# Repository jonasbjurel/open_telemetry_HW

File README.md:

# open_telemetry_HW

**Licenses:**

The official OpenFly Telemetry project(s) are all open source. The licensing may vary from GPL 2, GPL 3, Apache, or Creative Commons. As with many other hardware projects – OpenFly Telemetry comes with the Creative Commons - CC BY 2.0 license.

**Disclaimers:**

The use of any HW, SW or instructions from the OpenFly Telemetry open source project, or any references to other art - is at your own risk. No warranties, or legal obligations shall be assumed from the creators – in any way. Flying model planes, drones or other remotely controlled vehicles always impose danger to the surroundings – make all necessary precautions to make sure that no one is in danger even in case the control of your model is lost for whatever reason.

# Latest news
OFT001v1P1A* with sample BIST SW have declared it's first release candidate February 04 - 2020. First prototype full release is expected during February 2020. See the Wiki for mor information: https://github.com/jonasbjurel/open_telemetry_HW/wiki

# WIKI
 https://github.com/jonasbjurel/open_telemetry_HW/wiki

# OpenFly Telemetry overview
OpenFly Telemetry is an open source project aiming to provide telemetry and navigation capabilities for model airplanes and drones through open source hardware and software. It uses various on-board sensor capabilities such as GPS, Accelerometers, Gyroscopes, Magnetometers, Pitot tubes, temperature sensors, battery voltage and current sensors, RPM sensors, etc. to provide the operator or algorithms with data for manual or automated corrective actions. The algorithms are some time autonomous and resides in the model, are sometimes on ground with the receiver or nearby connected devices or are sometimes even in distant clouds.
The OFT modules can also be placed in the module bay of the transmitter to enrich the transmitter awareness, e.g. Position, direction and additional communication capabilities such as Bluetooth and WIFI conectivity.

**Figure 1:** OpenFly Telemetry basic idea

# OpenFly Telemetry (OFT) system description
OFT has two basic components: the Ada fruit ESP32 Huzzah feather processor board and the OFT system board. The ESP32 processor board obviously holds the software and algorithms for telemetry and navigation. The system board interfaces with the radio receiver and its telemetry and servo busses. The system is modular, and you can compose your choice of capabilities by stacking various OFT sensor boards on top of each other.

**Figure 2:** OpenFly Telemetry system view

OFT is based out of the Ada fruit ESP32 Huzzah feather processor board. This board hosts an ESP32 processor with two 32-bit general processor cores, 2 float processors and one ultra-low-power co-processor from Espressif (https://www.espressif.com/). Furthermore, the ESP32 board provides wireless connectivity through Bluetooth and WIFI as well as ensuring continuous power supply through an optional 2S designated LIPO, which could temporarily feed the servos and the receiver- should the main supply drain.
The ESP32 mother board connects to several telemetry acquisition boards in mother-daughter board/shield configurations.

**Figure 3:** Ada fruit ESP32 Huzzah feather board

For the on-board use cases (as opposed to the TX bay use case), the bottom most shield in the stack holds the OFT System board. The system board has an FPGA that connects to the radio receiver through the S.PORT for telemetry data, and the SBUS for servo output. The FPGA will allow the ESP32 processor to mix in servo corrections from the processor, transmitting upstream telemetry data, as well as receiving upstream telemetry and servo information from the transmitter. 
The system board interconnects with the radio control receiver through its S.PORT and SBUS.

**Figure 4:** Frsky XR4 2.4 GHz MIMO CDMA receiver with S.PORT- (telemetry) and SBUS (Servos) connections

# OpenFly Telemetry resources
## OpenFly Telemetry repositories
[OpenFly Telemetry main applications repository](https://github.com/jonasbjurel/open_telemetry)
This repository provides the application software repository for the OpenFly Telemetry project.

[OpenFly Telemetry hardware repository](https://github.com/jonasbjurel/open_telemetry_HW)
The repository for this project - providing HW blue-prints and designs for OpenFly Telemetry.

##  OpenFly Telemetry Dependencies
[ESP32 Arduino](https://github.com/espressif/arduino-esp32)
The Arduino port of Espressif ESP32.

[ESP32 FreeRTOS port documentation](https://docs.espressif.com/projects/esp-idf/en/latest/api-reference/system/freertos.html) FreeRTOS APIs and methods available for ESP32

[High availability- and embedded system FreeRTOS  shim layer](https://github.com/jonasbjurel/coreNoStopRTOS)
System initialization, process monitoring, memory management, system bus arbitration, inter process communication, and much more..

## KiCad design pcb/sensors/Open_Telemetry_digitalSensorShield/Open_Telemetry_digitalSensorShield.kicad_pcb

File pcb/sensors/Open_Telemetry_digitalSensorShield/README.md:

# OFT001v1 Inertial navigation board 
The OFT001v1 Inertial navigation board captures navigational data, such as GPS positioning, 3D acceleration data, 3D Gyroscopic data, 3D Magnetic data, Barometric pressure, Temperature and Humidity. Those data are provided to the ESP32 processor card (and any other shield cards) through I2C and RS232. The data will be filtered, processed and transferred by the ESP32 card and the OFT System card FPGA. It is still to be seen if we can/will implement a high-performance Inertial navigation fuse fixed point Kalman filter in the FPGA, or if it is better done in SW?

**Figure 5:** OFT001v1 Inertial navigation card overview

The OFT001v1 card has an L80-M39 GPS with a built-in patch antenna, and an optional connector for an external 50 Ohm active antenna; an MP-9250 3D axis for each of: Accelerometer, Gyroscope and Magnetometer; and a BMP280 Barometric pressure- humidity- and temperature sensor. Note that the axise's for the acelerometers and Gyrometers differs from those of the manetometers (x swaped with y, and neative Z), clearly marked on the board. The communication with these sensors have been segmented so that the MPU runs on its own high speed I2C channel, allowing fast updates, Kalman filtering-, integration- and Quaternion calculation cycles by the CPU (and possibly later offloaded by the OFT System card FPGA); the BMP280 is less latency critical, and shares an I2C channel with potentially other devices in the stack; while the GPS communication happens over an RS232 serial channel using extensions of the NMEA protocol.

There is one green LED indicator for GPS lock, one orange LED indictor for External GPS antenna use, and an RGB LED for generic system status indication driven from the ESP32 CPU board. There are also two push buttons: one which is connected to the overall system reset, and another multi-purpose push button intended for system calibration activities.

It is important that OFT001v1 sits on the top of the mother-daughter board stack (unless an external GPS antenna is used) in order to achieve a good GPS signal.
Cupper layers have been kept out from ESP32 Bluetooth and WIFI PCB antennas to not deteriorate the signal strength from those.

**Figure 6:** OFT001v1

?
## OFT001v1 shield pin-out

| OFT001 12 pin header (J2) | ESP32 HUZZAH 12 pin header (JP3) | ESP32 silicon | Comments               |
|---------------------------|----------------------------------|---------------|------------------------|
| 1 - N/C                   | VBAT                             | -             | N/C                    |
| 2 - N/C                   | EN                               | -             | N/C                    |
| 3 - N/C                   | VBUS                             | -             | N/C                    |
| 4  RED LED               | IO13_A12                         | 13 - IO13/A2_6| Red system status led  |
| 5  BLUE LED              | IO12_A11                         | 14  IO12/A2_5| Blue system status led |
| 6  GREEN LED             | IO27_A10                         | 12  IO27/A2_7| Green system status led|
| 7 - N/C                   | IO33_A9                          | 9 - IO33/A1_5 | N/C                    |
| 8 - N/C                   | IO15_A8                          | 23  IO15/A2_3| N/C                    |
| 9 - N/C                   | IO32_A7                          | 8  IO32/A1_4 | N/C                    |
| 10 - N/C                  | IO14_A6                          | 13  IO14/A2_6| N/C                    |
| 11 - I2C_0_SCL_3V         | SCL                              | 36  IO22     | Common non-critical I2C|
| 12 - I2C_0_SDA_3V         | SDA                              | 37  IO23     | Common non-critical I2C|

**Table 1:** J2 shield pin connector

| OFT001 16 pin header (J3) | ESP32 HUZZAH 16 pin header (JP1) | ESP32 silicon |Comments                   |
|---------------------------|----------------------------------|---------------|---------------------------|
| 1  INT_0                 | IO21                             | 33 - IO21     | Interrupt from MPU9250    |
| 2 - I2C_1_SDA_3V          | IO17                             | 28 - IO17     | Critical MPU I2C          |
| 3 - I2C_1_SCL_3V          | IO16                             | 27 - IO16     | Critical MPU I2C          |
| 4 - N/C                   | MISO                             | 31 - IO19     | N/C                       |
| 5 - N/C                   | MOSI                             | 30 - IO18     | N/C                       |
| 6 - N/C                   | SCK                              | 29 - IO5      | N/C                       |
| 7 - CALIB                 | A5_IO4                           | 26 - IO4/A2_2 | System calibration button |
| 8 - UART_1_CLIENT_RXD     | A4_IO36                          | 4 - IO36/A1_0 | L8-M39 GPS UART (NMEA)    |
| 9 - UART_1_CLIENT_TXD     | A3_I39                           | 5  IO39/A1_3 | L8-M39 GPS UART (NMEA)    |
| 10  N/C                  | A2_I34                           | 6  I34/A1_6  | N/C                       |
| 11  N/C                  | A1_DAC1                          | 10  IO25/DAC1/A2_8| N/C                  |
| 12  N/C                  | A0_DAC2                          | 11  IO26/DAC2/A2_9| N/C                  |
| 13 - GND                  | GND                              | -	       | GND from ESP32 motherboard|
| 14  N/C                  | N/C                              | -             | N/C                       |
| 15 - +3.3V (VDD)          | +3.3V                            | -             | 3.3V max 120 mA from ESP32 motherboard (rated for max ???)|
| 16 - RESET                | RESET                            | 3 - EN        | 2-Way reset               |

**Table 2:** J3 shield pin connector

| OFT001 Ext GPS Ant. (J1) | Comments                                                              |
|--------------------------|-----------------------------------------------------------------------|
| 1  AGND                 | External active GPS antenna ground                                    |
| 2  EXTANT               | External active GPS antenna signal with VDD DC applied for power feed |

**Table 3:** J1 External PS Antenna

## OFT001v1 addressing

| I2CBus | Addr	           | Function | Comments |
|--------|-----------------|----------|----------|
| 0	 | 0x77(0x761) (1) | BME280   | -        |
| 1      | 0x68(0x692) (2) | MPU9250  | -        |

1)	Alternative address if NULL resistor R4 is mounted (not default)
2)	Alternative address if NULL resistor R7 is mounted (not default)

**Table 4:** OFT001v1 I2C addressing

## OFT001 v1 operating specifications
### Operational conditions:

| Parameter          | Nom    | Max     | Min      |
|--------------------|--------|---------|----------|
| Voltage            | 3.3 V  | 3.6 V   | 3.0 V    |
| Current            | 30 mA  | 120 mA  | -        |
| Power dissipation  | 100 mW | 400 mW  | -        |
| Ambient temp       | -      | 85 degC | -40 degC |

**Table 5:** OFT001v1 Operational conditions

### GPS antenna operational conditions:
The built in GPS patch antenna provides the following characteristics:

**Figure 7:** OFT001v1 Built in L80-M39 path GPS antenna characteristics

External GPS antenna operational requirements:

| Parameter            | Value          |
|----------------------|----------------|
| DC feed:             | 3.6V  2.5V    |
| DC current (max):    | <???           |
| Center frequency:    | 1575.42MHz     |
| Band width:          | >5MHz          |
| VSWR:                | <2 (Typ.)      |
| Polarization:        | RHCP or Linear |
| Noise figure:        | <1.5dB         |
| Gain (antenna):      | >-2dBi         |
| Gain (embedded LNA): | 20dB (Typ.)    |
| Total gain:          | >18dBi (Typ.)  |

**Table 6:** OFT001v1 External operational conditions

## OFT001v1 schematics

**Figure 8:** OFT001v1 schematics

## OFT001v1 - third party data sheets

[L80-M39 GPS receiver](http://docs-emea.rs-online.com/webdocs/147d/0900766b8147dbf2.pdf)

[BME280 Barometric pressure sensor](https://ae-bst.resource.bosch.com/media/_tech/media/datasheets/BST-BME280-DS002.pdf)

[MPU9250 9-Axis Accelerometer, Gyroscope and Magenetometer](http://43zrtwysvxb2gf29r5o0athu-wpengine.netdna-ssl.com/wp-content/uploads/2015/02/PS-MPU-9250A-01-v1.1.pdf)

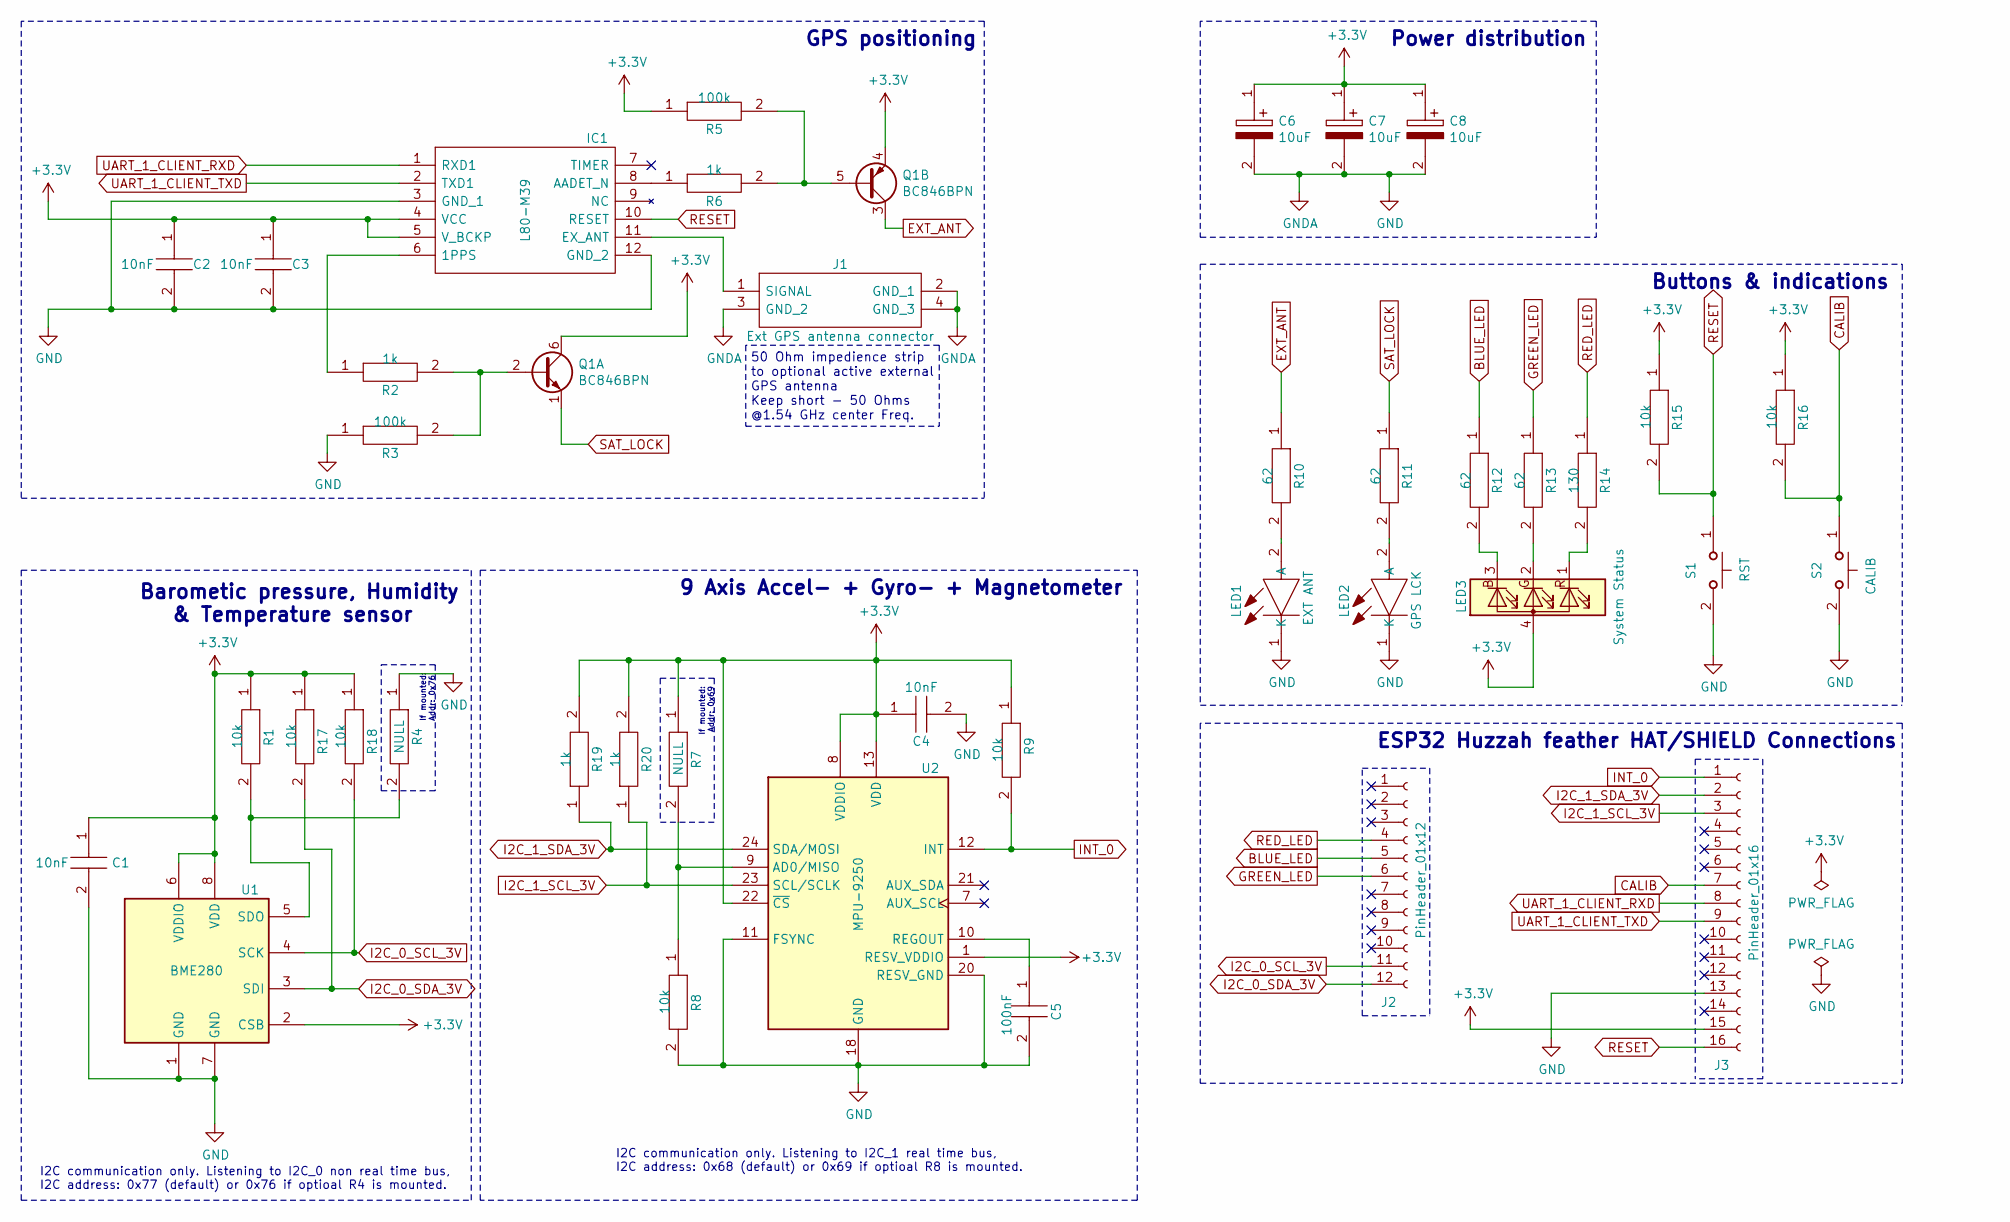
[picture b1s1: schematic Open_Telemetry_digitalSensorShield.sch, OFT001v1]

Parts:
C1, C2, C3, C4: 10nF; CAPC1608X87N; Manufacturer_Part_Number C0603C103K4RACTU; Mouser Part Number 80-C0603C103K4R
C5: 100nF; CAPC1005X55N; Manufacturer_Part_Number C0402C104M8RACTU; Mouser Part Number 80-C0402C104M8R
C6, C7, C8: 10uF; CAPPM3528X210N; Manufacturer_Part_Number T491B106K016AT7280; Mouser Part Number 80-T491B106K16AT7280
IC1: L80-M39; Manufacturer_Part_Number L80-M39
J1: Ext GPS antenna connector; U.FL_Molex_MCRF_73412-0110_Vertical; Manufacturer_Part_Number 73412-0110; Mouser Part Number 538-73412-0110
J2: PinHeader_01x12; PinHeader_1x12_P2.54mm_Vertical_Down
J3: PinHeader_01x16; PinHeader_1x16_P2.54mm_Vertical_Down
LED1: EXT ANT; LEDC1608X65N; Manufacturer_Part_Number SML-D13DWT86A; Mouser Part Number 755-SML-D13DWT86A
LED2: GPS LCK; SMLD15YWT86; Manufacturer_Part_Number SML-D13FWT86; Mouser Part Number 755-SML-D13FWT86
LED3: System Status; AVAGO_PLCC4
Q1: BC846BPN; SOT-363_SC-70-6
R1, R8, R9, R15, R16, R17, R18: 10k; RESC0603X26N; Manufacturer_Part_Number RC0201JR-0710KL; Mouser Part Number 603-RC0201JR-0710KL
R2, R6, R19, R20: 1k; RESC0603X26N; Manufacturer_Part_Number RC0201JR-071KL; Mouser Part Number 603-RC0201JR-071KL
R3, R5: 100k; RESC0603X26N; Manufacturer_Part_Number RC0201JR-07100KL; Mouser Part Number 603-RC0201JR-07100KL
R4, R7: NULL; RESC0603X26N; Manufacturer_Part_Number RC0201JR-070RL; Mouser Part Number 603-RC0201JR-070RL
R10, R11, R12, R13: 62; RESC1005X40N; Manufacturer_Part_Number RC0402JR-0762RL; Mouser Part Number 603-RC0402JR-0762RL
R14: 130; RESC1005X40N; Manufacturer_Part_Number CRCW0402130RJNED; Mouser Part Number 71-CRCW0402130RJNED
S1: RST; KSR; Manufacturer_Part_Number KSR223GLFG; Mouser Part Number 611-KSR223GLFG
S2: CALIB; KSR; Manufacturer_Part_Number KSR223GLFG; Mouser Part Number 611-KSR223GLFG
U1: BME280; Bosch_LGA-8_2x2.5mm_P0.65mm_ClockwisePinNumbering
U2: MPU-9250; 3DInvenSense_QFN-24_3x3mm_P0.4mm

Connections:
+3V3: C1.1, C2.1, C3.1, C4.1, C6.1, C7.1, C8.1, IC1.4 (VCC), IC1.5 (V_BCKP), J3.15, LED3.4 (A), Q1.4 (E2), Q1.6 (C1), R1.1, R5.1, R7.1, R9.1, R15.1, R16.1, R17.1, R18.1, R19.2, R20.2, U1.2 (CSB), U1.6 (VDDIO), U1.8 (VDD), U2.1 (RESV_VDDIO), U2.8 (VDDIO), U2.13 (VDD), U2.22 (~CS)
BLUE_LED: J2.5, R12.1
CALIB: J3.7, R16.2, S2.1
EXT_ANT: Q1.3 (C2), R10.1
GND: C1.2, C2.2, C3.2, C4.2, C5.2, C6.2, C7.2, C8.2, IC1.3 (GND_1), IC1.12 (GND_2), J1.2 (GND_1), J1.3 (GND_2), J1.4 (GND_3), J3.13, LED1.1 (K), LED2.1 (K), R3.1, R4.1, R8.2, S1.2, S2.2, U1.1 (GND), U1.7 (GND), U2.11 (FSYNC), U2.18 (GND), U2.20 (RESV_GND)
GREEN_LED: J2.6, R13.1
I2C_0_SCL_3V: J2.11, R18.2, U1.4 (SCK)
I2C_0_SDA_3V: J2.12, R17.2, U1.3 (SDI)
I2C_1_SCL_3V: J3.3, R20.1, U2.23 (SCL/SCLK)
I2C_1_SDA_3V: J3.2, R19.1, U2.24 (SDA/MOSI)
INT_0: J3.1, R9.2, U2.12 (INT)
unnamed: C5.1, U2.10 (REGOUT)
unnamed: IC1.6 (1PPS), R2.1
unnamed: IC1.8 (AADET_N), R6.1
unnamed: IC1.11 (EX_ANT), J1.1 (SIGNAL)
unnamed: LED1.2 (A), R10.2
unnamed: LED2.2 (A), R11.2
unnamed: LED3.1 (RK), R14.2
unnamed: LED3.2 (GK), R13.2
unnamed: LED3.3 (BK), R12.2
unnamed: Q1.2 (B1), R2.2, R3.2
unnamed: Q1.5 (B2), R5.2, R6.2
unnamed: R1.2, R4.2, U1.5 (SDO)
unnamed: R7.2, R8.1, U2.9 (AD0/MISO)
RED_LED: J2.4, R14.1
RESET: IC1.10 (RESET), J3.16, R15.2, S1.1
SAT_LOCK: Q1.1 (E1), R11.1
UART_1_CLIENT_RXD: IC1.1 (RXD1), J3.8
UART_1_CLIENT_TXD: IC1.2 (TXD1), J3.9

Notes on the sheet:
ESP32 Huzzah feather HAT/SHIELD Connections
Buttons & indications
Power distribution
GPS positioning
Barometic pressure, Humidity & Temperature sensor
If mounted: Addr: 0x76
If mounted: Addr: 0x69
9 Axis Accel- + Gyro- + Magnetometer
I2C communication only. Listening to I2C_0 non real time bus, I2C address: 0x77 (default) or 0x76 if optioal R4 is mounted.
I2C communication only. Listening to I2C_1 real time bus, I2C address: 0x68 (default) or 0x69 if optioal R8 is mounted.
50 Ohm impedience strip to optional active external GPS antenna Keep short - 50 Ohms @1.54 GHz center Freq.

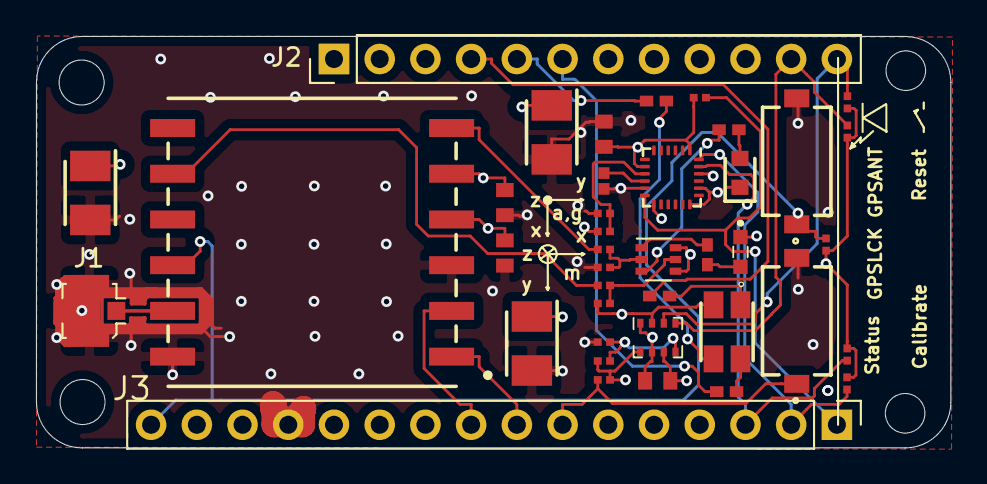
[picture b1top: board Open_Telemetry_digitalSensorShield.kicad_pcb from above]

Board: 4 copper layers, 50.8 x 22.9 mm, 44 parts (0 on the bottom side), 29 nets.

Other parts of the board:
P1, P2: MountingHole_2.5mm
P3, P4: MountingHole_2.2mm_M2

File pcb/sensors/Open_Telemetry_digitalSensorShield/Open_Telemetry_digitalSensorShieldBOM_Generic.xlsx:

Reference: OpenFly Telemetry - OFT001v1 P1A_BOM Rev.:P1A_02
Item # | Ref Des | Qty | Manufacturer | Mfg Part # | Description / Value | Package | Type | Footprint | Datasheet | Stock price quote source | Stock Price singeltons (Eur) | Sub total Stock Price (Eur)
1 | C1, C2, C3, C4 | 4 | Kemet | C0603C103K4RACTU | CAP, 0.01F, 16V, 10%, X7R | 0603 | SMD | Open_Telemetry:CAPC1608X87N | https://api.kemet.com/component-edge/download/datasheet/C060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 | https://www.mouser.com/Search/Refine.aspx?Keyword=80-C0603C103K4R | 0.09 | 0.36
2 | C5 | 1 | Kemet | C0402C104M8RACTU | CAP, 0.1uF, 10V, 20%, X7R | 0402 | SMD | Open_Telemetry:CAPC1005X55N | https://content.kemet.com/datasheets/KEM_C1002_X7R_SMD.pdf | https://www.mouser.com/Search/Refine.aspx?Keyword=80-C0402C104M8R | 0.09 | 0.09
3 | C6, C7, C8 | 3 | Kemet | T491B106K016AT7280 | Tantalum CAP, 10uF, 16V, 10%, ESR=2ohms | 1311 | SMD | CAPPM3528X210N | https://api.kemet.com/component-edge/download/datasheet/T491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 | https://www.mouser.com/Search/Refine.aspx?Keyword=80-T491B10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 | 0.41399999999999998 | 1.242
4 | IC1 | 1 | Quectel Wireless Solutions | L80-M39 | L80 GPS Module | 12-LCC-2.4mm-16mm | SMD | Open_Telemetry:L80-M39 | http://docs-emea.rs-online.com/webdocs/147d/0900766b8147dbf2.pdf | https://uk.rs-online.com/web/p/products/9084085/ | 12 | 12
5 | J1 | 1 | Molex | 73412-0110 | 50 Ohms, MCRF, PCB Vertical Jack Receptacle | SMT | SMD | Open_Telemetry:U.FL_Molex_MCRF_73412-0110_Vertical | http://www.molex.com/pdm_docs/sd/734120110_sd.pdf | https://www.mouser.com/Search/Refine.aspx?Keyword=538-73412-0110 | 0.63 | 0.63
6 | J2 | 1 | Harwin | M20-9991245 | PinHeader_01x12 2.54 mm pitch | 12 POS | Thru-hole | Open_Telemetry:PinHeader_1x12_P2.54mm_Vertical_Down | https://eu.mouser.com/ProductDetail/Harwin/M20-9991245?qs=%2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 | https://eu.mouser.com/ProductDetail/Harwin/M20-9991245?qs=%2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 | 0.41399999999999998 | 0.41399999999999998
7 | J3 | 1 | Harwin | M20-9991645 | PinHeader_01x16 2.54 mm pitch | 16 POS | Thru-hole | Open_Telemetry:PinHeader_1x16_P2.54mm_Vertical_Down | https://eu.mouser.com/ProductDetail/Harwin/M20-9991645?qs=%2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 | https://eu.mouser.com/ProductDetail/Harwin/M20-9991645?qs=%2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 | 0.55000000000000004 | 0.55000000000000004
8 | LED1 | 1 | ROHM Semiconductor | SML-D13DWT86A | Orange LED | 0603 | SMD | Open_Telemetry:LEDC1608X65N | https://docs-emea.rs-online.com/webdocs/156b/0900766b8156b2c9.pdf | https://www.mouser.com/Search/Refine.aspx?Keyword=755-SML-D13DWT86A | 0.41 | 0.41
9 | LED2 | 1 | ROHM Semiconductor | SML-D13FWT86 | Green LED | 0603 | SMD | Open_Telemetry:SMLD15YWT86 | http://www.rohm.com/web/global/datasheet/SML-D13FW/sml-d13x-e | https://www.mouser.com/Search/Refine.aspx?Keyword=755-SML-D13FWT86 | 0.36 | 0.36
10 | LED3 | 1 | Avago | ASMB-MTB1-0A3A2 | Tricolor black surface RGB surfacce LED | PLCC4 | SMD | Open_Telemetry:AVAGO_PLCC4 | https://docs.broadcom.com/docs/AV02-4194EN | https://eu.mouser.com/ProductDetail/Broadcom-Avago/ASMB-MTB1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 | 0.51 | 0.51
11 | Q1 | 1 | Nexperia | BC846BPN, 115 | NPN/PNP transistor | SOT363 | SMD | Package_TO_SOT_SMD:SOT-363_SC-70-6 | https://assets.nexperia.com/documents/data-sheet/BC846BPN.pdf | https://eu.mouser.com/ProductDetail/Nexperia/BC846BPN115?qs=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 | 0.28999999999999998 | 0.28999999999999998
12 | R1, R8, R9, R15, R16, R17, R18 | 7 | YAGEO (PHYCOMP) | RC0201JR-0710KL | RES, THICK FILM, 10K, 5%, 0.05W | 0201 | SMD | Open_Telemetry:RESC0603X26N | https://www.ttiinc.com/content/ttiinc/en/apps/part-detail.ht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 | https://www.mouser.com/Search/Refine.aspx?Keyword=603-RC0201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 | 0.09 | 0.45
13 | R2, R6, R19, R20 | 4 | YAGEO (PHYCOMP) | RC0201JR-071KL | RES, THICK FILM, 1K, 5%, 0.05W | 0201 | SMD | Open_Telemetry:RESC0603X26N | https://www.ttiinc.com/content/ttiinc/en/apps/part-detail.ht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 | https://www.mouser.com/Search/Refine.aspx?Keyword=603-RC0201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 | 0.09 | 0.18
14 | R3, R5 | 2 | YAGEO (PHYCOMP) | RC0201JR-07100KL | RES, THICK FILM, 100K, 5%, 0.05W | 0201 | SMD | Open_Telemetry:RESC0603X26N | https://www.ttiinc.com/content/ttiinc/en/apps/part-detail.ht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 | https://www.mouser.com/Search/Refine.aspx?Keyword=603-RC0201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 | 0.09 | 0.18
15 | R10, R11, R12, R13 | 4 | YAGEO (PHYCOMP) | RC0402JR-0762RL | RES, THICK FILM, 62R, 5%, 0.125W | 0402 | SMD | Open_Telemetry:RESC1005X40N | https://www.ttiinc.com/content/ttiinc/en/apps/part-detail.ht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 | https://www.mouser.com/Search/Refine.aspx?Keyword=603-RC0402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 | 0.09 | 0.36
16 | R14 | 1 | Vishay | CRCW0402130RJNED | RES,THICK FILM, 130R, 5% 0.063 W | 0402 | SMD | Open_Telemetry:RESC1005X40N | https://www.ttiinc.com/content/ttiinc/en/apps/part-detail.ht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 | https://www.mouser.com/Search/Refine.aspx?Keyword=71-CRCW040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 | 0.09 | 0.09
17 | S1, S2 | 2 | C & K COMPONENTS | KSR223GLFG | RST, CALIB Tactile Switches 1VA, 32VDC, IP50 | SMT | SMD | Open_Telemetry:KSR | https://dznh3ojzb2azq.cloudfront.net/products/Tactile/KSR/do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 | https://eu.mouser.com/ProductDetail/CK/KSR223GLFG?qs=%2Fha2p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 | 0.82799999999999996 | 1.6559999999999999
18 | U1 | 1 | Bosh | BME280 | Barrometic pressure sensor | 2.5mmx2.5mmx093mm metal lid LGA | SMD | Open_Telemetry:Bosch_LGA-8_2x2.5mm_P0.65mm_ClockwisePinNumbering | https://ae-bst.resource.bosch.com/media/_tech/media/datashee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 | https://eu.mouser.com/Search/Refine?Keyword=BME280 | 3.36 | 3.36
19 | U2 | 1 | InvenSense | MPU-9250 | 9 Axis MPU | QFN-24_3x3mm | SMD | Open_Telemetry:3DInvenSense_QFN-24_3x3mm_P0.4mm | http://43zrtwysvxb2gf29r5o0athu-wpengine.netdna-ssl.com/wp-c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 | https://www.digikey.se/product-detail/sv/tdk-invensense/MPU-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 | 2.6 | 2.6
DO NOT MOUNT:
20 | R4, R7 | 2 | YAGEO (PHYCOMP) | RC0201JR-070RL | RES, THICK FILM, 0R, 5%, 0.05W | 0201 | SMD | RESC0603X26N | https://www.ttiinc.com/content/ttiinc/en/apps/part-detail.ht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 | https://www.mouser.com/Search/Refine.aspx?Keyword=603-RC0201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 | - | -
Total: | # Unique comp | # Comp. |  |  |  |  | SMD / Thru |  |  |  |  | Tot Stock price
 | 19 | 38 |  |  |  |  | 36/2 |  |  |  |  | 25.731999999999999

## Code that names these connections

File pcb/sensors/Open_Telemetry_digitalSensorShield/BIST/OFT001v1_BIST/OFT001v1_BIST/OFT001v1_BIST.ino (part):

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/* ****************************************************************************************************
   ESP32 Huzza Feather PIN definitions (ESP32 Wroom)                                                  *
***************************************************************************************************** */
#define CALIB_PIN  4
#define RED_LED_PIN 13
#define BLUE_LED_PIN 12
#define GREEN_LED_PIN 27
#define I2C_0_SCL_PIN 22
#define I2C_0_SDA_PIN 23
#define I2C_1_SCL_PIN 16
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//The setup function runs once when you press reset or power on the board
void setup() {
	Serial.begin(115200);
	pinMode(CALIB_PIN, INPUT);
	pinMode(MPU_INTERRUPT_PIN, INPUT);

	// Create the BLE Device
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	//Setup the LEDs
	ledcSetup(RED_LED_CH, freq, resolution);
	ledcWrite(RED_LED_CH, (pow(2, resolution) - 0));
	ledcAttachPin(RED_LED_PIN, RED_LED_CH);
	
	ledcSetup(BLUE_LED_CH, freq, resolution);
	ledcWrite(BLUE_LED_CH, (pow(2, resolution) - 0));
	ledcAttachPin(BLUE_LED_PIN, BLUE_LED_CH);

	ledcSetup(GREEN_LED_CH, freq, resolution);
	ledcWrite(GREEN_LED_CH, (pow(2, resolution) - 0));
	ledcAttachPin(GREEN_LED_PIN, GREEN_LED_CH);

	I2C_0.begin(I2C_0_SDA_PIN, I2C_0_SCL_PIN, 100000);
	I2C_1.begin(I2C_1_SDA_PIN, I2C_1_SCL_PIN, 100000);
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
	//BIST Testing the Callib button
	case CALIB_BUTTON_TEST:
		if (digitalRead(CALIB_PIN)) {
			consolePrint(".");
			if (timeout >= 20) {
				consolePrintln("");
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
	//BIST Testing and callibrating LEDs
	case STATUS_LED_TEST:
		if (calibDebounce && !digitalRead(CALIB_PIN)) {
			break;
		}
		if (calibDebounce && digitalRead(CALIB_PIN)) {
			calibDebounce = 0;
		}
		switch (ledColorCalib) {
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			if (!ledRedLuminance)
				consolePrintln("Calibrating status LEDs, starting with RED, press the calibration button when satisfied with the Luminance");

			if (!digitalRead(CALIB_PIN) || (ledRedLuminance >= pow(2, resolution))) {
				consolePrint("RED led is calibrated to: ");
				gcvt((100 * ledRedLuminance / pow(2, resolution)), 2, calibTextVal);
				consolePrint(calibTextVal);
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			if (!ledBlueLuminance) {
				consolePrintln("Continuing with BLUE, press the calibration button when satisfied with the Luminance");
			}
			if (!digitalRead(CALIB_PIN) || (ledBlueLuminance >= pow(2, resolution))) {
				consolePrint("BLUE led is calibrated to: ");
				gcvt((100 * ledBlueLuminance / pow(2, resolution)), 2, calibTextVal);
				consolePrint(calibTextVal);
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			if (!ledGreenLuminance) {
				consolePrintln("Continuing with GREEN, press the calibration button when satisfied with the Luminance");
			}
			if (!digitalRead(CALIB_PIN) || (ledGreenLuminance >= pow(2, resolution))) {
				consolePrint("GREEN led is calibrated to: ");
				gcvt((100 * ledGreenLuminance / pow(2, resolution)), 2, calibTextVal);
				consolePrint(calibTextVal);
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		ledcWrite(GREEN_LED_CH, (pow(2, resolution) - ledGreenLuminance));
		if (GPS.newNMEAreceived())
			GPS.parse(GPS.lastNMEA());
		if ((GPS.fix && (GPSAltCalib = GPS.altitude)) || (!digitalRead(CALIB_PIN))) {
			consolePrintln("Satelites aquired, Calibrating the system....");
			BarTempCalib();
			ledcWrite(RED_LED_CH, (pow(2, resolution) - ledRedLuminance));
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
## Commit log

2019-11-07 First version of the digital sensor board routed.
2019-11-12 2'nd internal review
2019-11-15 OFT001v1 Inertial HW board ready for internal review. Find it underpcb/sensors/Open_Telemetry_digitalSensorShield/...
2019-11-18 First candidate for prototype manufacturing of OFT001 P1A01 sent to PCBWay after a early feedback. Close to manufacturing goahead.
2019-11-19 This was suposed to be the last commit going into P1A prototype manufacturing, but there are likely missing pull-ups for the 2 I2C busses needing correction. Probably a 1k pullup for the high speed M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
2019-11-20 P1A02 files sent to manufactuing review. Added R17, R18, R19, RR20 I2C pullups for reliability and hiher speeds.
2019-11-21 Corrected the PCBWAY BOM
2019-11-21 Updated documentation and pictures
2019-11-21 Another picture added
2019-11-21 Added picture for patch antenna char
2019-11-22 README's and LICENCE's updated
2019-12-12 Corrected the error where BME280 was placed as U1 instead of BMP280 This is the baseline that will be delivered as the P1A prototype card.
2020-01-20 First BIST Self-test ESP32 program for the OFT001V1 P1A module - not elegant - but working it's purpose to evaluate the sensor module - which it does fine!
2020-01-24 BIST fully functional
2020-01-25 Fixed OFT001v1 BIST GPS reading issues
2020-01-25 Fixed OFT001v1 BIST GPS reading issues (from master)
2020-01-28 OFT001 v1 documentation updated
2020-01-28 OFT001 v1 documentation updated (Cherry picked from master)
2020-02-04 BIST library dependencies explisitly added to the repository. A few BIST bugs fixed.
2020-02-04 BIST library dependencies explisitly added to the repository. A few BIST bugs fixed. Cherry-picked from master
2020-02-04 OFT001v1P1A Release Candidate #1 (RC1) Updated documentation Minor update on the streaming console handling
2020-02-04 OFT001v1P1A Release Candidate #1 (RC1) Updated documentation Minor update on the streaming console handling Cherrypicked from master...

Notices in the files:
pcb/sensors/Open_Telemetry_digitalSensorShield/BIST/OFT001v1_BIST/OFT001v1_BIST/OFT001v1_BIST.ino:
(c) Copyright 2020 Jonas Bjurel (jonasbjurel@hotmail.com)
Licensed under the Apache License, Version 2.0 (the "License");
Unless required by applicable law or agreed to in writing, software distributed under the License
README.md:
https://upload.wikimedia.org/wikipedia/commons/1/16/CC-BY_icon.svg
pcb/sensors/Open_Telemetry_digitalSensorShield/Open_Telemetry_digitalSensorShield.kicad_pcb:
© 2019 - Jonas Bjurel
License: Creative commons - CC BY 2.0
